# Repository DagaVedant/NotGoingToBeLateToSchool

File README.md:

# NotGoingToBeLateToSchool

a 9 key alarm clock that makes you type a code to shut it up.

built on a xiao esp32c3 for BLARE. during the day it sits on my desk cycling through
weather, hackatime hours, now playing and world clocks. at 6am it tells my phone to start
playing spotify instead of screaming at me with a piezo. you get 3 snoozes, and on the 3rd
one you have to type a code on the keypad before it stops.

every alarm clock i've had is useless for the 16 hours a day you're awake, and way too easy
to snooze into oblivion. this one tries to fix both.

the top plate and the pcb share hardware: one m3x16 screw per corner runs down through the
top plate boss and the board into the same heatset insert the pcb post already carries, so
there's no separate top-plate insert or screw anymore. simpler, but the board can't come out
without pulling the top plate first. the bosses sit over the board, so they need a bit of
support when printing the base.

the pcb sits on four posts that land exactly on its mounting holes. the xiao is socketed on
the underside, so its usb-c port ends up 13mm below the board, and the slot in the back wall
is cut around that spot, not at board height.

## what it does

**ambient**, all day

- auto rotates through weather / hackatime hours / now playing / world clocks
- spinning globe on the clock face, same animation as the oled on my hackpad
- one small json from a relay covers all four pages, so the clock makes one https request
  a minute instead of juggling four apis itself

**alarm**, at 6am

- multiple alarms, each with its own days of the week, all editable on the device
- 3 snoozes max. the first two are normal, on the 3rd it drops into code entry and keeps
  going until you type the right code
- screen fades up from near black to full brightness over the 15 min before the alarm
- escalating piezo buzzer that speeds up the longer you ignore it

**ble**, written and compiling, never run on hardware

- pairs as a ble media remote so the alarm hits play on my phone instead of buzzing
- iphone notifications over ancs

## the board

69.5 x 97mm, 2 layers, 25 footprints. 461 tracks, 14 vias, about 1.5m of copper. drc clean,
nothing unrouted.

- keys on the top side at 19.05 pitch so the caps clear each other
- xiao and display header on the underside, so the top face is just keycaps and the buzzer
- xiao at the back with usb-c out the rear, on 2.54 sockets so it can be pulled out
- 8 pin display header at the front edge so the jumper run to the screen is short
- one diode per switch, sitting in the 3.45mm gap directly below it
- 4x m3 mounting holes, pushed out to the corners so they clear the key block

the routed layout in kicad, red is the front copper and blue is the back:

and a 3d render of the same board:

nine switches in a 3x3 matrix, one 1n4148 per key so holding two keys down cannot ghost a
third.

## bom

| part | qty |
|------|-----|
| seeed xiao esp32c3 | 1 |
| st7789 tft (76×284) | 1 |
| cherry mx pcb-mount switches | 9 |
| mx keycaps | 9 |
| 1n4148 diodes | 9 |
| piezo buzzer (12×9.5, rm7.6) | 1 |
| 1×08 2.54mm pin socket (display) | 1 |
| 1×07 2.54mm pin sockets (xiao) | 2 |
| m3×16 screws | 4 |
| m3 heatset inserts | 4 |

same list in [BOM.csv](BOM.csv).

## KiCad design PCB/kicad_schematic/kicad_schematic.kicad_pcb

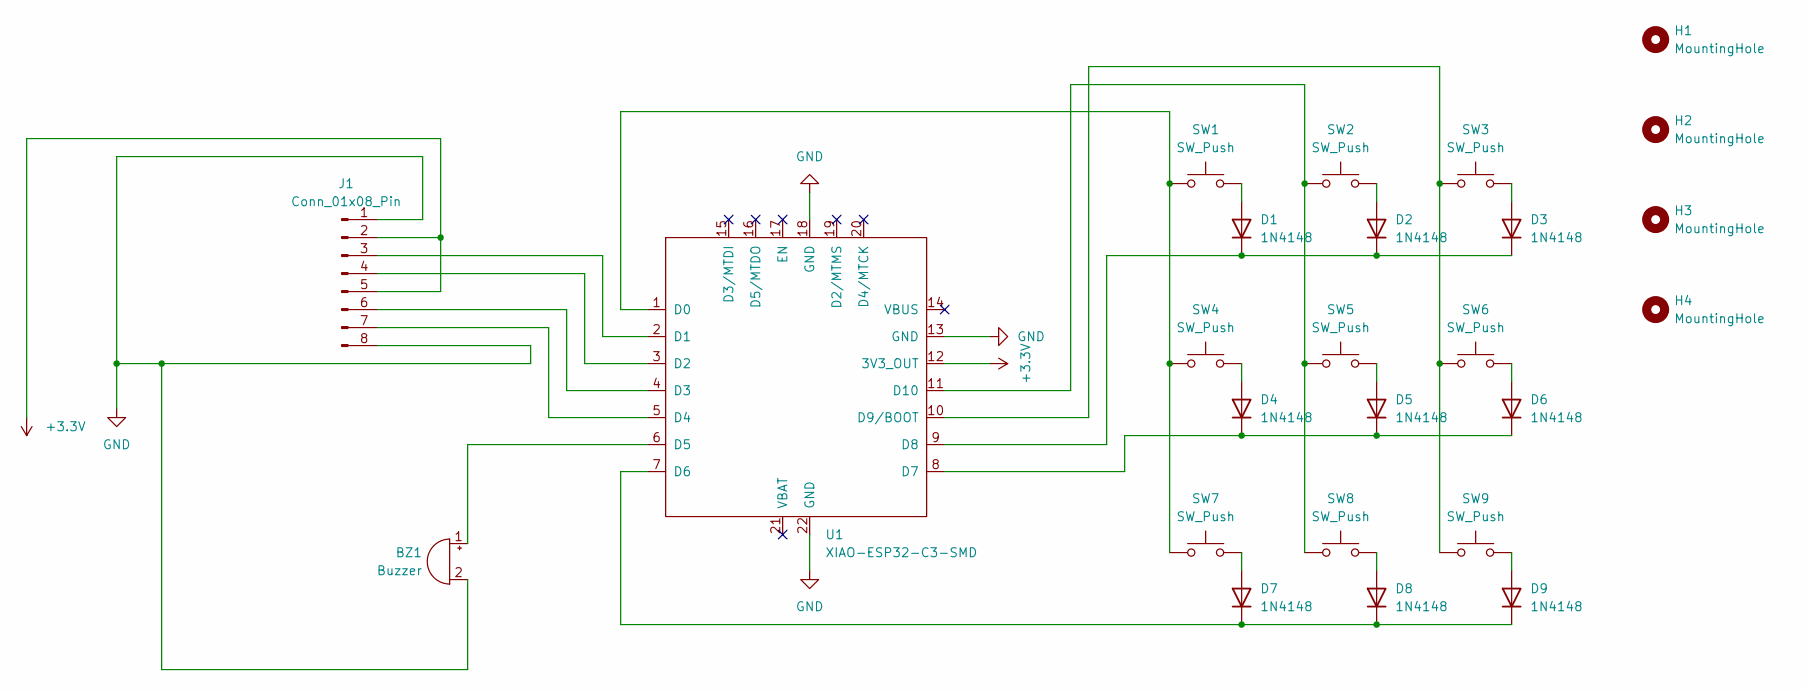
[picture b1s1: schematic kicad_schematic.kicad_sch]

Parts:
BZ1: Buzzer; Buzzer_12x9.5RM7.6
D1, D2, D3, D4, D5, D6, D7, D8, D9: 1N4148; D_DO-35_SOD27_P7.62mm_Horizontal
H1, H2, H3, H4: MountingHole; MountingHole_3.2mm_M3
J1: Conn_01x08_Pin; PinSocket_1x08_P2.54mm_Vertical
SW1, SW2, SW3, SW4, SW5, SW6, SW7, SW8, SW9: SW_Push; SW_Cherry_MX_1.00u_PCB
U1: XIAO-ESP32-C3-SMD; XIAO-ESP32-C3-DIP

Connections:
+3.3V: J1.2, J1.5, U1.12 (3V3_OUT)
GND: BZ1.2 (-), J1.1, J1.8, U1.13 (GND), U1.18 (GND), U1.22 (GND)
unnamed: BZ1.1 (+), U1.6 (D5)
unnamed: D1.2 (A), SW1.2
unnamed: D1.1 (K), D2.1 (K), D3.1 (K), U1.9 (D8)
unnamed: D2.2 (A), SW2.2
unnamed: D3.2 (A), SW3.2
unnamed: D4.2 (A), SW4.2
unnamed: D4.1 (K), D5.1 (K), D6.1 (K), U1.8 (D7)
unnamed: D5.2 (A), SW5.2
unnamed: D6.2 (A), SW6.2
unnamed: D7.2 (A), SW7.2
unnamed: D7.1 (K), D8.1 (K), D9.1 (K), U1.7 (D6)
unnamed: D8.2 (A), SW8.2
unnamed: D9.2 (A), SW9.2
unnamed: J1.3, U1.2 (D1)
unnamed: J1.4, U1.3 (D2)
unnamed: J1.6, U1.4 (D3)
unnamed: J1.7, U1.5 (D4)
unnamed: SW1.1, SW4.1, SW7.1, U1.1 (D0)
unnamed: SW3.1, SW6.1, SW9.1, U1.10 (D9/BOOT)
unnamed: SW2.1, SW5.1, SW8.1, U1.11 (D10)

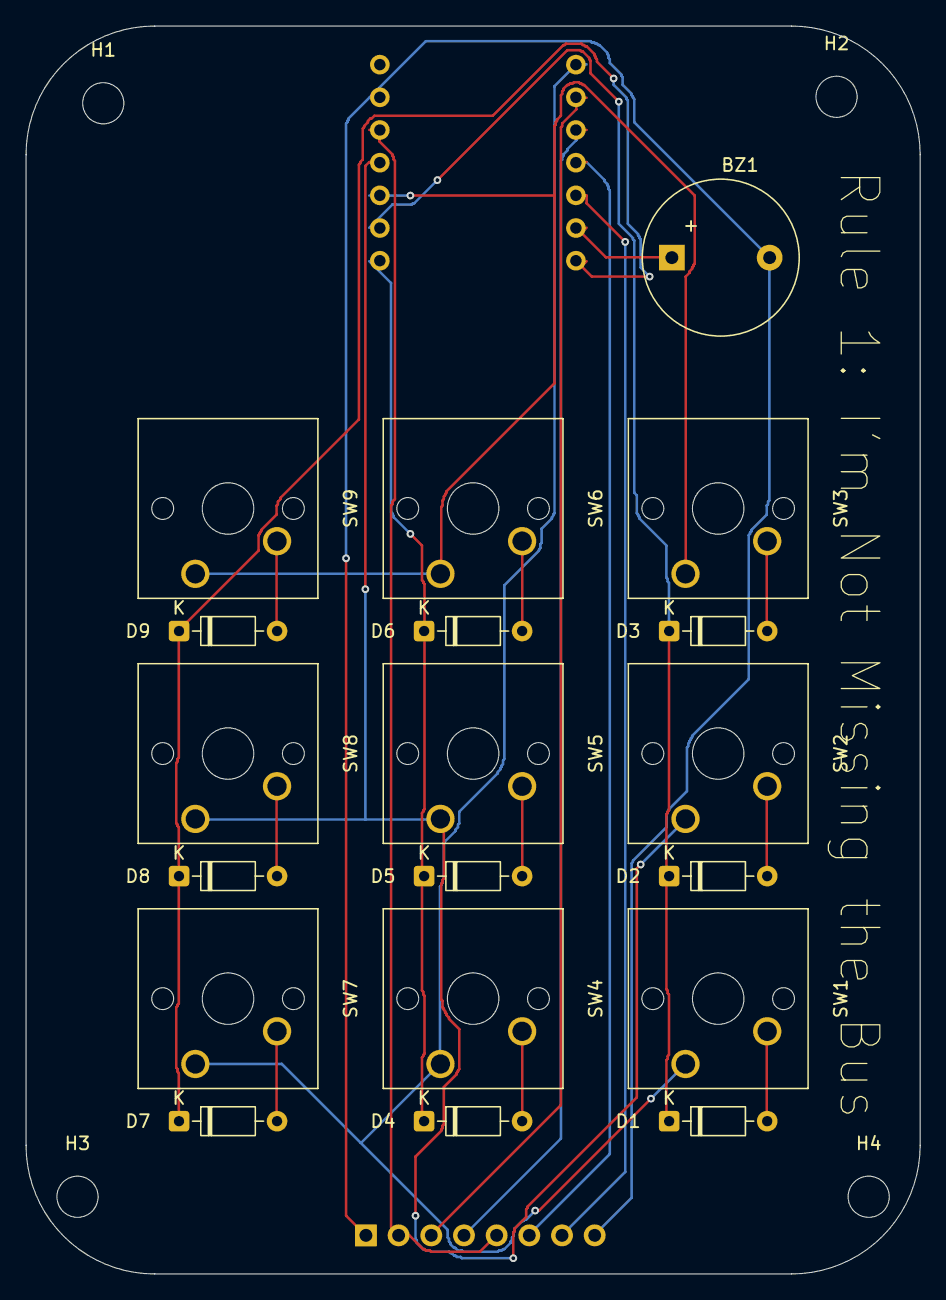
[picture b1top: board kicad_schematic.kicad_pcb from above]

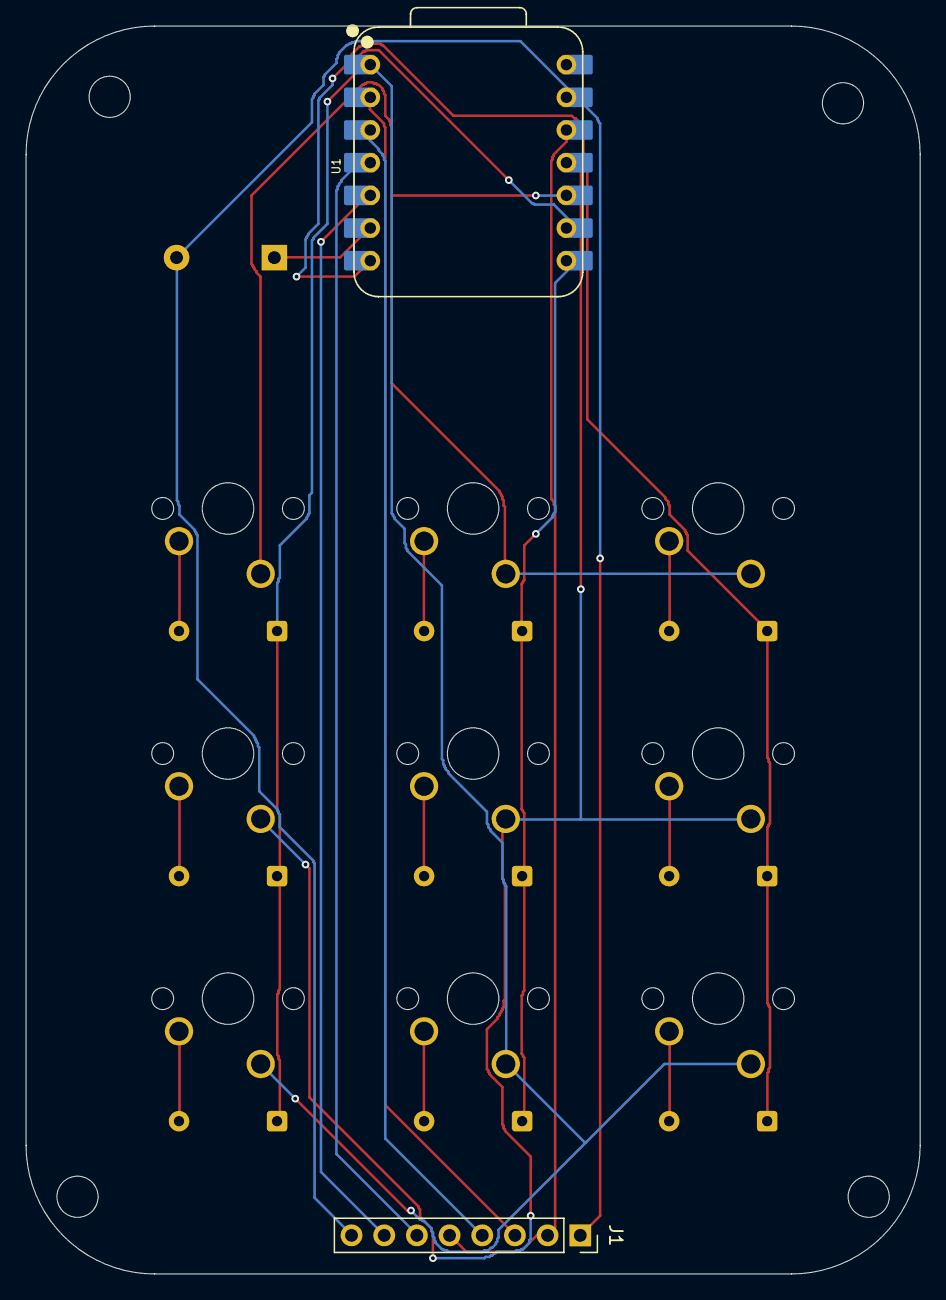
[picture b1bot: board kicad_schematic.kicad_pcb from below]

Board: 2 copper layers, 69.5 x 97.0 mm, 25 parts (2 on the bottom side), 22 nets.
